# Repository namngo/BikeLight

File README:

Led controller chip:
https://www.monolithicpower.com/en/documentview/productdocument/index/version/2/document_type/Datasheet/lang/en/sku/MP2410/document_id/2079
https://www.monolithicpower.com/en/documentview/productdocument/index/version/2/document_type/Datasheet/lang/en/sku/EV2410-J-00A/document_id/2797/

## Part links

### Screens
* Screen: https://www.aliexpress.us/item/3256804050802693.html?spm=a2g0o.order_list.order_list_main.81.6dc41802Oe7kPv&gatewayAdapt=glo2usa#nav-specification

### ESP32

#### Esp32 super mini

* ESP32 module: https://www.aliexpress.us/item/3256810393697250.html?spm=a2g0o.order_list.order_list_main.29.6dc41802Oe7kPv&gatewayAdapt=glo2usa#nav-specification

```
Product parameter

Powerful CPU: ESP32-S3, 32-bit RISC-V single-core processor, running at up to 160 MHz

WiFi: 802.11b/g/n protocol, 2.4GhHz, support Station mode, SoftAP mode, SoftAP+Station mode, hybrid mode

Bluetooth: Bluetooth 5.0

Ultra-low power consumption: deep sleep power consumption of about 43μA

Rich board resources: 400KB SRAM, 384KB ROM built-in 4Mflash.

Chip model: ESP32S3FH4R2

Ultra-small size: As small as the thumb (22.52x18mm) classic shape, suitable for wearables and small projects

Reliable security features: Encryption hardware accelerators that support AES-128/256, hashing, RSA, HMAC, digital signatures, and secure startup

Rich interface: 1xI2C, 1xSPI, 2xUART, 11xGPIO(PWM), 4xADC

Onboard RGB, blue LED: common GPIO 48 pin

```

## Research

https://michaelmanning.ca/e-paper-climate-logger/

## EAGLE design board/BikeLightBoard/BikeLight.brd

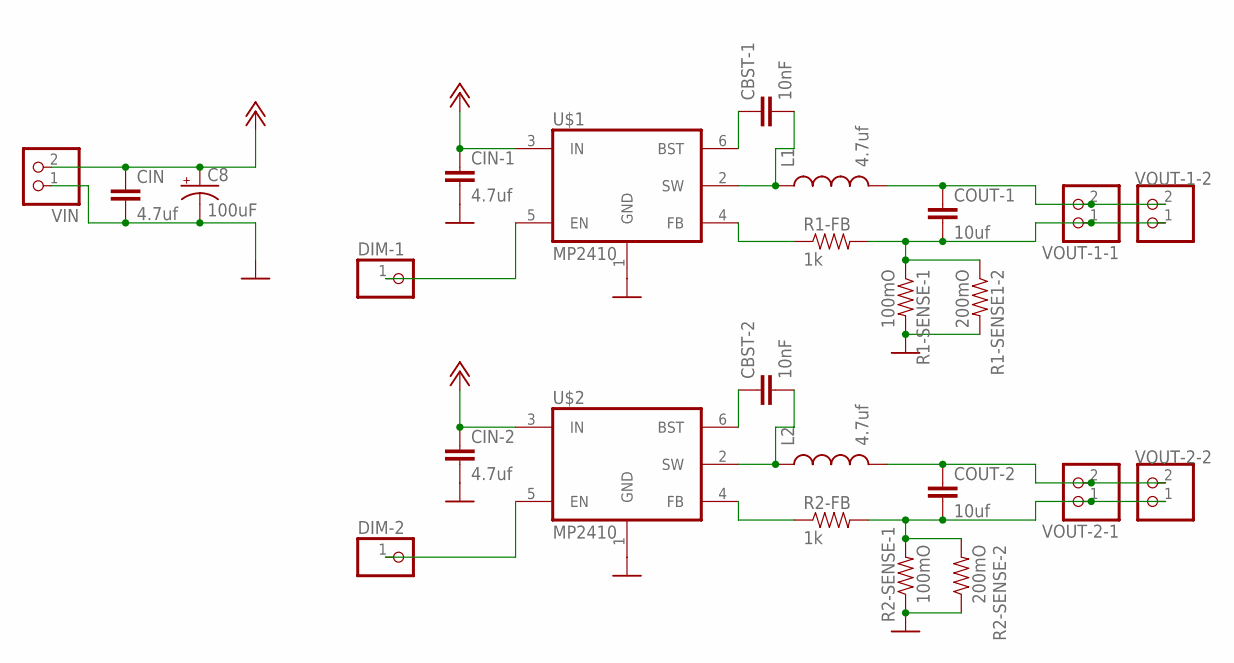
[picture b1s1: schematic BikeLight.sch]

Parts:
C8: 100uF; NIC_10X10.5_CAP
CBST-1, CBST-2: 10nF; 0805
CIN: 4.7uf; 1206
CIN-1, CIN-2: 4.7uf; 1206
COUT-1, COUT-2: 10uf; 1210
DIM-1, DIM-2: PINHD-1X1; 1X01
L1, L2: 4.7uf; RLB0912
R1-FB, R2-FB: 1k; 0805
R1-SENSE1-2, R2-SENSE-2: 200mO; 1206
R1-SENSE-1, R2-SENSE-1: 100mO; 1206
U$1, U$2: MP2410; TSOT23-6
VIN: PINHD-1X2; 1X02
VOUT-1-1, VOUT-1-2, VOUT-2-1, VOUT-2-2: PINHD-1X2; 1X02

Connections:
+12V: C8.+, CIN.1, CIN-1.1, CIN-2.1, U$1.3 (IN), U$2.3 (IN), VIN.2
GND: C8.-, CIN.2, CIN-1.2, CIN-2.2, R1-SENSE1-2.2, R1-SENSE-1.2, R2-SENSE-1.1, R2-SENSE-2.1, U$1.1 (GND), U$2.1 (GND), VIN.1
unnamed: DIM-2.1, U$2.5 (EN)
unnamed: DIM-1.1, U$1.5 (EN)
unnamed: CBST-1.2, L1.1, U$1.2 (SW)
unnamed: CBST-2.2, L2.1, U$2.2 (SW)
unnamed: CBST-1.1, U$1.6 (BST)
unnamed: R1-FB.1, U$1.4 (FB)
unnamed: R2-FB.1, U$2.4 (FB)
unnamed: CBST-2.1, U$2.6 (BST)
N-OUT-1-N: COUT-1.2, R1-FB.2, R1-SENSE1-2.1, R1-SENSE-1.1, VOUT-1-1.1, VOUT-1-2.1
N-OUT-1-P: COUT-1.1, L1.2, VOUT-1-1.2, VOUT-1-2.2
N-OUT-2-N: COUT-2.2, R2-FB.2, R2-SENSE-1.2, R2-SENSE-2.2, VOUT-2-1.1, VOUT-2-2.1
N-OUT-2-P: COUT-2.1, L2.2, VOUT-2-1.2, VOUT-2-2.2

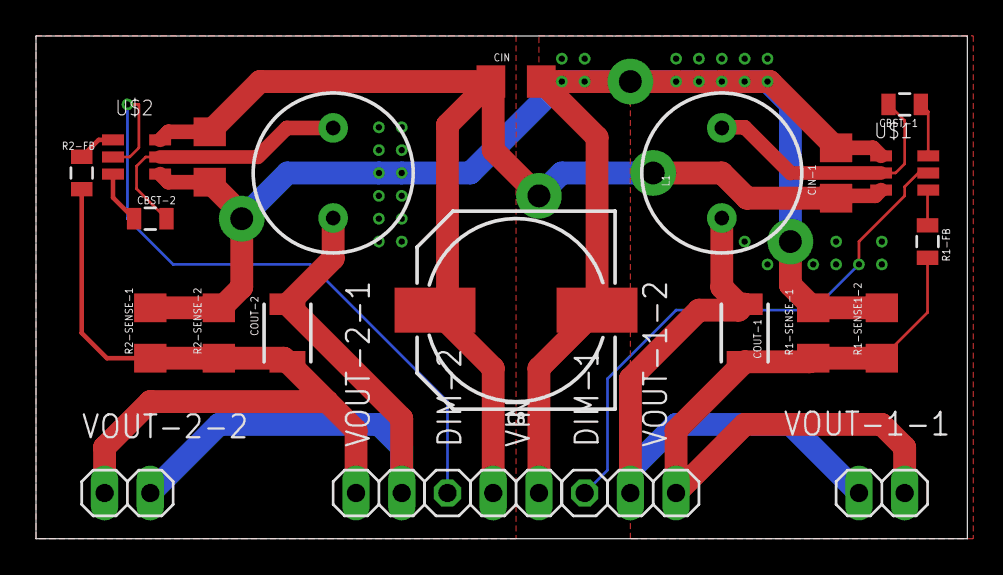
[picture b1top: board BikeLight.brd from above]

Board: 2 copper layers, 51.7 x 27.9 mm, 25 parts (0 on the bottom side), 14 nets.

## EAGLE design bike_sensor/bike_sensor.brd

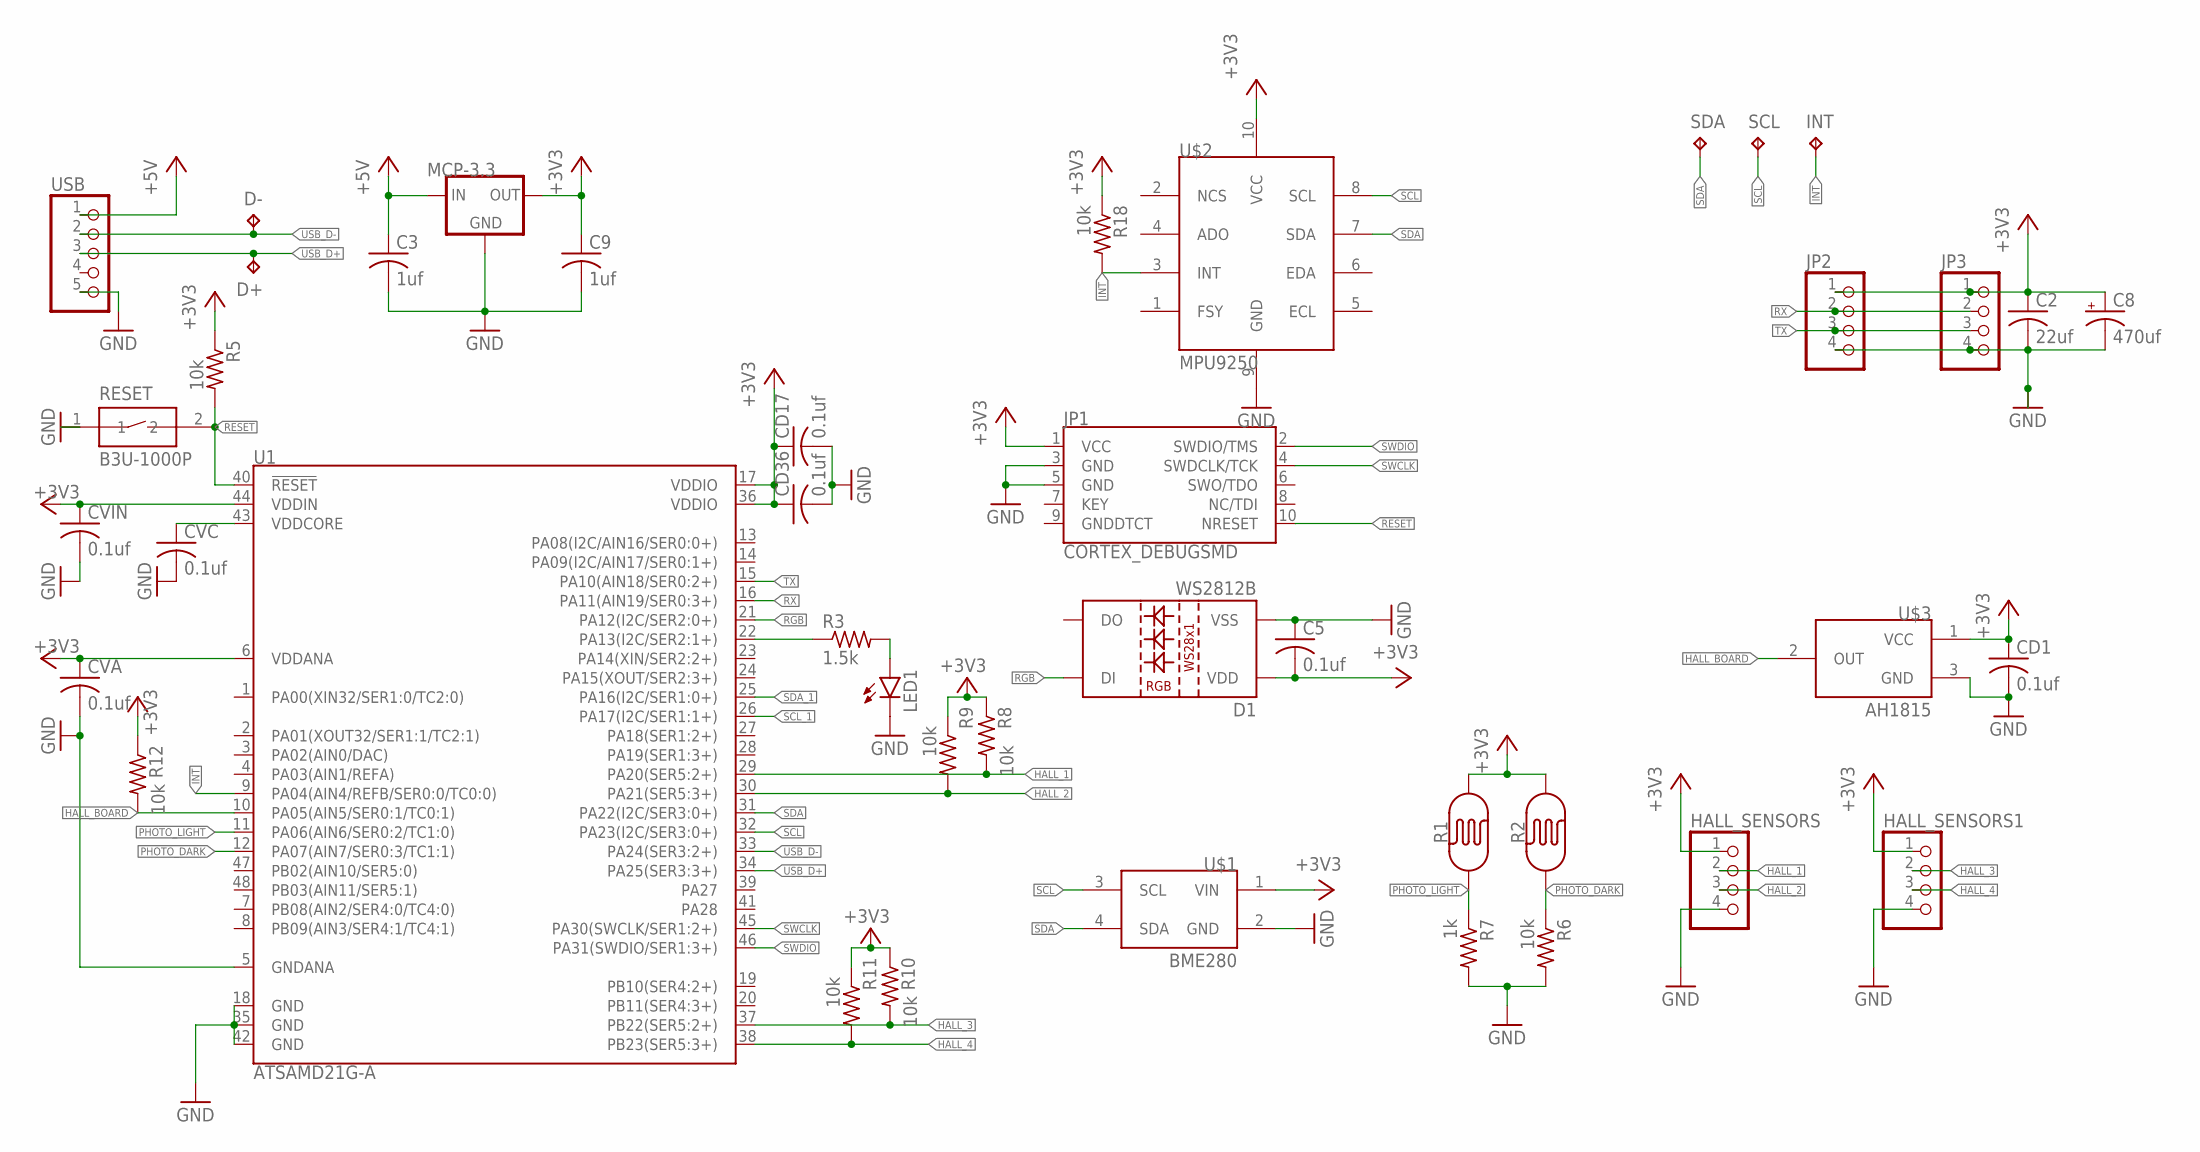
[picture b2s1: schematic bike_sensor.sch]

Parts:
C2: 22uf; C1210
C3, C9: 1uf; C1210
C5: 0.1uf; C0805
C8: 470uf; UD-8X10_NICHICON
CD1, CD17, CD36: 0.1uf; C0805
CVA: 0.1uf; C0805
CVC: 0.1uf; C0805
CVIN: 0.1uf; C0805
D1: WS2812B
D+: TPB1,27; B1,27
D-: TPB1,27; B1,27
HALL_SENSORS, HALL_SENSORS1: PINHD-1X4; 1X04
INT: TPB1,27; B1,27
JP1: CORTEX_DEBUGSMD; SAMTECH_FTSH-105-01
JP2, JP3: PINHD-1X4; 1X04
LED1: LEDCHIPLED_0805; CHIPLED_0805
MCP-3.3: XC63FPM; SOT23
R1, R2: PHOTOCELLPTH; PHOTOCELL
R3: 1.5k; R0805
R5, R6, R8, R9, R10, R11, R12, R18: 10k; R0805
R7: 1k; R0805
RESET: B3U-1000P
SCL: TPB1,27; B1,27
SDA: TPB1,27; B1,27
U1: ATSAMD21G-A; TQFP-48
U$1: BMP280; BME280-BOARD
U$2: MPU9250; ICM-20948-BOARD
U$3: AH1815; SOT23
USB: PINHD-1X5; 1X05

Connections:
+3V3: C2.1, C5.2, C8.+, C9.1, CD1.1, CD17.1, CD36.1, CVA.1, CVIN.1, D1.1 (VDD), HALL_SENSORS.1, HALL_SENSORS1.1, JP1.1 (VCC), JP2.1, JP3.1, MCP-3.3.2 (OUT), R1.2, R2.2, R5.1, R8.1, R9.1, R10.1, R11.1, R12.1, R18.1, U1.6 (VDDANA), U1.17 (VDDIO), U1.36 (VDDIO), U1.44 (VDDIN), U$1.1 (VIN), U$2.10 (VCC), U$3.1 (VCC)
+5V: C3.1, MCP-3.3.3 (IN), USB.1
GND: C2.2, C3.2, C5.1, C8.-, C9.2, CD1.2, CD17.2, CD36.2, CVA.2, CVC.2, CVIN.2, D1.3 (VSS), HALL_SENSORS.4, HALL_SENSORS1.4, JP1.3 (GND), JP1.5 (GND), JP2.4, JP3.4, LED1.C, MCP-3.3.1 (GND), R6.2, R7.2, RESET.1, U1.5 (GNDANA), U1.18 (GND), U1.35 (GND), U1.42 (GND), U$1.2 (GND), U$2.9 (GND), U$3.3 (GND), USB.5
HALL_1: HALL_SENSORS.2, R8.2, U1.29 (PA20(SER5:2+))
HALL_2: HALL_SENSORS.3, R9.2, U1.30 (PA21(SER5:3+))
HALL_3: HALL_SENSORS1.2, R10.2, U1.37 (PB22(SER5:2+))
HALL_4: HALL_SENSORS1.3, R11.2, U1.38 (PB23(SER5:3+))
HALL_BOARD: R12.2, U1.10 (PA05(AIN5/SER0:1/TC0:1)), U$3.2 (OUT)
INT: INT.TP, R18.2, U1.9 (PA04(AIN4/REFB/SER0:0/TC0:0)), U$2.3 (INT)
unnamed: CVC.1, U1.43 (VDDCORE)
unnamed: R3.1, U1.22 (PA13(I2C/SER2:1+))
unnamed: LED1.A, R3.2
PHOTO_DARK: R2.1, R6.1, U1.12 (PA07(AIN7/SER0:3/TC1:1))
PHOTO_LIGHT: R1.1, R7.1, U1.11 (PA06(AIN6/SER0:2/TC1:0))
RESET: JP1.10 (NRESET), R5.2, RESET.2, U1.40 (!RESET!)
RGB: D1.4 (DI), U1.21 (PA12(I2C/SER2:0+))
RX: JP2.2, JP3.2, U1.16 (PA11(AIN19/SER0:3+))
SCL: SCL.TP, U1.32 (PA23(I2C/SER3:0+)), U$1.3 (SCL), U$2.8 (SCL)
SCL_1: U1.26 (PA17(I2C/SER1:1+))
SDA: SDA.TP, U1.31 (PA22(I2C/SER3:0+)), U$1.4 (SDA), U$2.7 (SDA)
SDA_1: U1.25 (PA16(I2C/SER1:0+))
SWCLK: JP1.4 (SWDCLK/TCK), U1.45 (PA30(SWCLK/SER1:2+))
SWDIO: JP1.2 (SWDIO/TMS), U1.46 (PA31(SWDIO/SER1:3+))
TX: JP2.3, JP3.3, U1.15 (PA10(AIN18/SER0:2+))
USB_D+: D+.TP, U1.34 (PA25(SER3:3+)), USB.3
USB_D-: D-.TP, U1.33 (PA24(SER3:2+)), USB.2

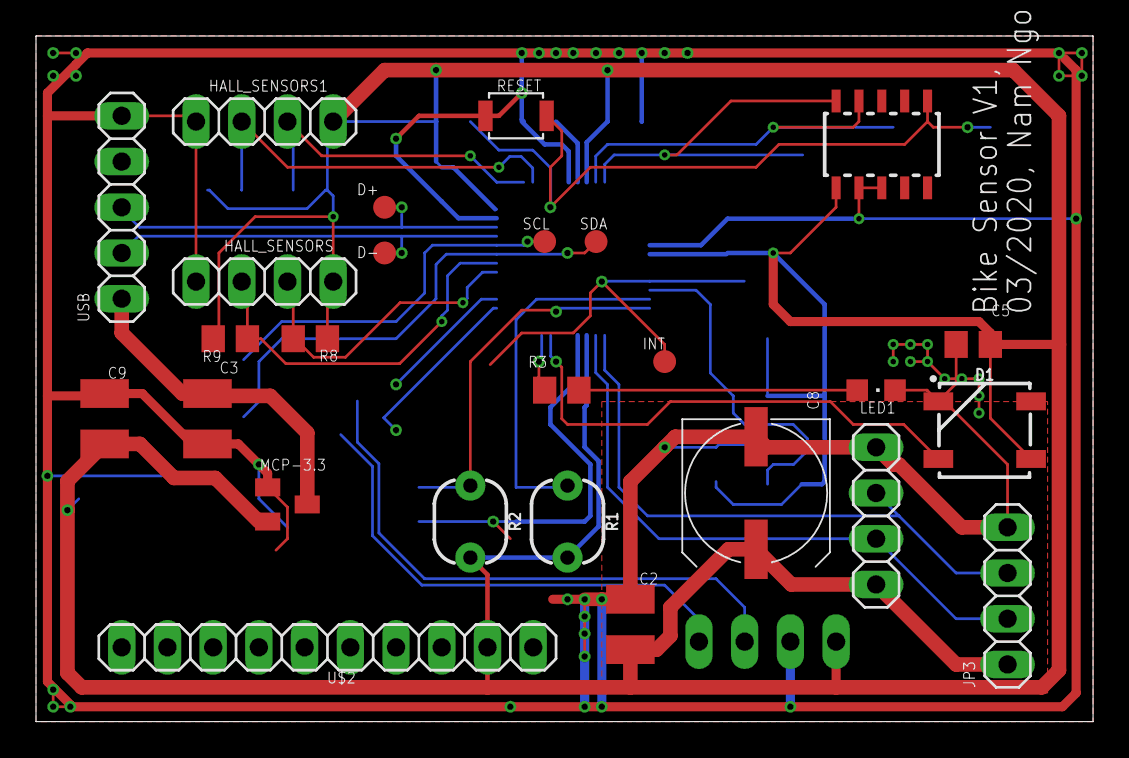
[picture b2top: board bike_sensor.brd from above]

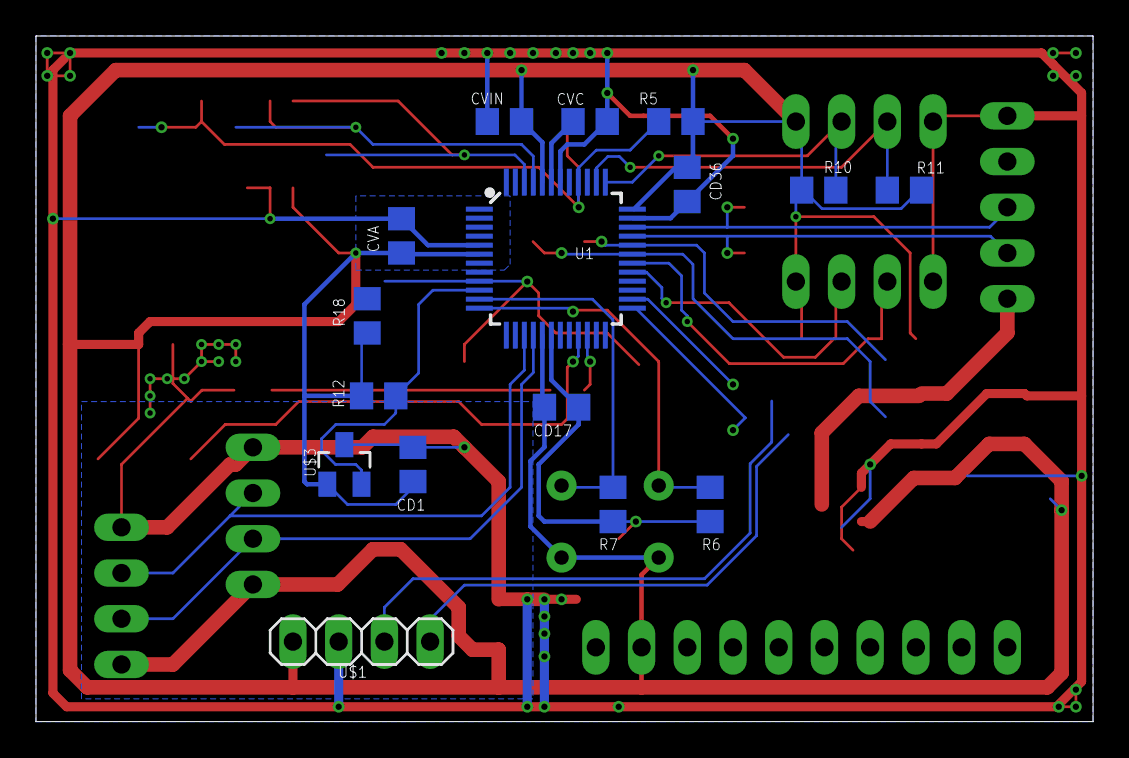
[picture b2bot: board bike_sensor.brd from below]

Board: 2 copper layers, 58.7 x 38.1 mm, 42 parts (16 on the bottom side), 24 nets.

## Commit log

2019-11-02 add readme
2019-11-06 finish board
2019-11-06 finishing touch
2020-04-02 library
2020-04-03 arduino settings
2020-04-04 debuging i2c
2020-04-06 sensors working
2020-04-06 try new icm library
2020-04-07 change to new lib
2020-04-07 add new icm lib
2020-04-08 remove 1.8v
2020-04-08 update mpu9250
2020-04-09 use mpu
2020-04-10 change
2020-04-15 stringstream
2020-04-20 esp32
2020-04-20 Try sparkfun dmp
2020-04-20 borderflight mpu9250
2020-04-20 calibrated
2020-04-20 got data
2020-04-20 remove icm20948 files
2020-04-20 add mpu9250 lib
2020-04-20 remove icm code
2025-12-26 esp32 s3
2025-12-29 add kicad board
2025-12-29 add new bike board
2025-12-30 finish working today
2026-01-02 remove old bikeboards
2026-01-02 Revert "remove old bikeboards"
    This reverts commit a9e1404b7c4aa93456804174a9f9b6465af947c2.
2026-01-02 remove old eagle board
2026-01-06 mp2410
2026-01-09 code
2026-01-20 clean up for mp2410
2026-01-20 mp2410 boards
2026-01-20 done basic board
2026-01-20 finish the board
2026-01-20 light
2026-01-22 remove export files
2026-01-22 remove old directoy
2026-01-22 export to pdf
2026-01-27 add parts
2026-02-04 main board
2026-03-05 new board
2026-04-09 add esp32

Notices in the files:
parts and their libraries:
SparkFun-Sensors: Licensing: Creative Commons ShareAlike 4.0 International - https://creativecommons.org/licenses/by-sa/4.0
